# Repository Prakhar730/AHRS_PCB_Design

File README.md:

<div align="center">

# PCB Design for an Attitude and Heading Reference System (AHRS)

### A custom 4-layer PCB featuring an STM32 MCU and a 9-axis IMU, developed during a research internship at the Indian Institute of Technology, Kanpur.

</div>

---

Welcome to the official repository for my AHRS project. This project documents the complete hardware design cycle—from component selection and circuit simulation to final PCB layout—for a custom Attitude and Heading Reference System. It was developed as the primary focus of my six-week internship in the Department of Electrical Engineering at IIT Kanpur.

> The goal of this project was to apply theoretical knowledge of electronics and embedded systems to a practical challenge: creating a compact, reliable, and manufacturable PCB for high-performance orientation sensing in robotics and navigation applications.

---

## Table of Contents
1.  [Key Features](#-key-features)
2.  [Repository Structure](#-repository-structure)
3.  [Technical Specifications](#-technical-specifications)
4.  [Challenges & Solutions](#-challenges--solutions)
5.  [Contact & Acknowledgments](#-contact--acknowledgments)

---

##  Key Features

-   **High-Performance Sensing**: Integrates the `LSM9DS1` 9-axis IMU, which includes a 3-axis accelerometer, 3-axis gyroscope, and 3-axis magnetometer on a single chip.
-   **Powerful Processing**: Driven by an `STM32F401RET6` ARM Cortex-M4 microcontroller, providing ample computational power for real-time sensor fusion algorithms.
-   **Stable Power Management**: Features an onboard `TPS62172` buck converter to efficiently step down 5V from USB to a clean 3.3V supply, validated through LTspice simulations.
-   **Robust Connectivity**: Equipped with a `CP2102` USB-to-UART bridge for straightforward data streaming, programming, and debugging.
-   **Optimized 4-Layer PCB**: The layout is designed for a compact form factor while maintaining excellent signal integrity and noise immunity through dedicated ground and power planes.

---

##  Repository Structure

The project files are organized into two primary directories, separating the hardware design from the circuit simulation.

```
AHRS-PCB-Design/
├── PCB + Schematics/
│   ├── AHRSNEW.kicad_pro
│   ├── AHRSNEW.kicad_sch
│   └── AHRSNEW.kicad_pcb
│
└── Power Supply Simulation/
    └── Draft1.asc
```
-   **`PCB + Schematics/`**: This directory contains the complete KiCad project, including all source files for the schematic design and the final 4-layer PCB layout.
-   **`Power Supply Simulation/`**: This directory holds the LTspice simulation files used to validate the power supply circuit before finalizing the hardware design.

---

##  Technical Specifications

### Hardware Components

| Component         | Part Number       | Description                                                 |
| :---------------- | :---------------- | :---------------------------------------------------------- |
| **Microcontroller** | `STM32F401RET6`     | ARM Cortex-M4 MCU for processing sensor data.               |
| **IMU Sensor** | `LSM9DS1`         | 9-axis motion sensor (accelerometer, gyroscope, magnetometer). |
| **Buck Converter** | `TPS62172`        | Efficiently steps down 5V USB power to a stable 3.3V.       |
| **USB-UART Bridge** | `CP2102`          | Provides a communication interface with a host computer.    |

### Software & Tools

-   **PCB Design**: KiCad (Schematic Capture & PCB Layout)
-   **Circuit Simulation**: LTspice (Power Supply Validation)

---

##  Challenges & Solutions

-   **Interpreting Complex Datasheets**
    -   *Solution*: Adopted a structured approach, breaking down datasheets section-by-section and cross-referencing with application notes and online forums.

-   **Achieving a Stable Power Supply**
    -   *Solution*: The power supply circuit was simulated in LTspice to validate component choices and ensure stable operation before hardware implementation.

-   **PCB Layout & Signal Integrity**
    -   *Solution*: Followed standard PCB best practices, including using differential pair routing for USB, keeping high-speed traces short, and utilizing ground planes to shield signals.

---

##  Contact & Acknowledgments

This project was completed under the expert supervision of Prof. Yatindra Nath Singh at IIT Kanpur. I extend my sincere gratitude to my mentors, Mr. Nagendra Kumar and Mr. Rahul Bhattacharyya, for their continuous technical guidance and support.

Feel free to connect with me to discuss this project or other topics in embedded systems and robotics.

-   **LinkedIn**: [My LinkedIn Profile URL](https://www.linkedin.com/in/prakhar-sharma-75b998347/)
-   **GitHub**: [My GitHub Profile URL](https://github.com/Prakhar730)
-   **Email**: [My Mail](sprakhar2005@gmail.com)

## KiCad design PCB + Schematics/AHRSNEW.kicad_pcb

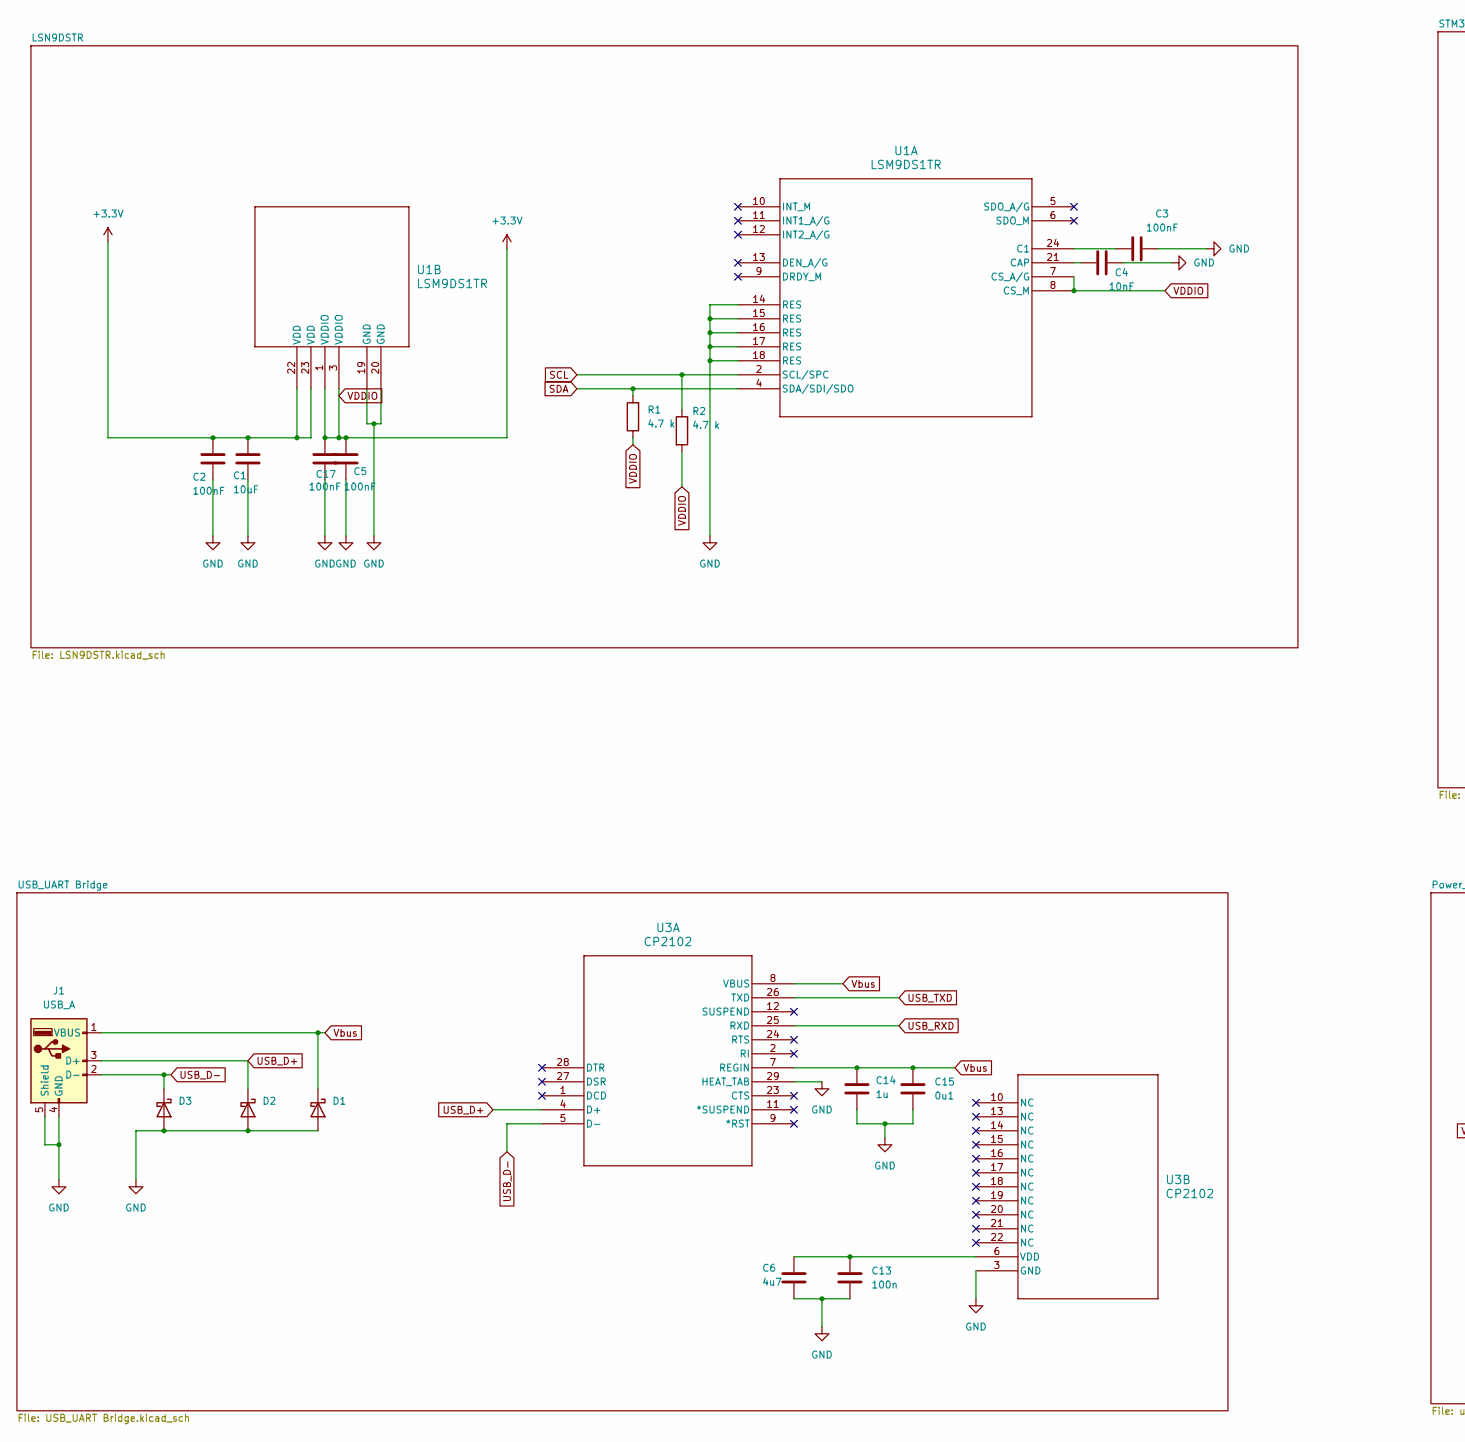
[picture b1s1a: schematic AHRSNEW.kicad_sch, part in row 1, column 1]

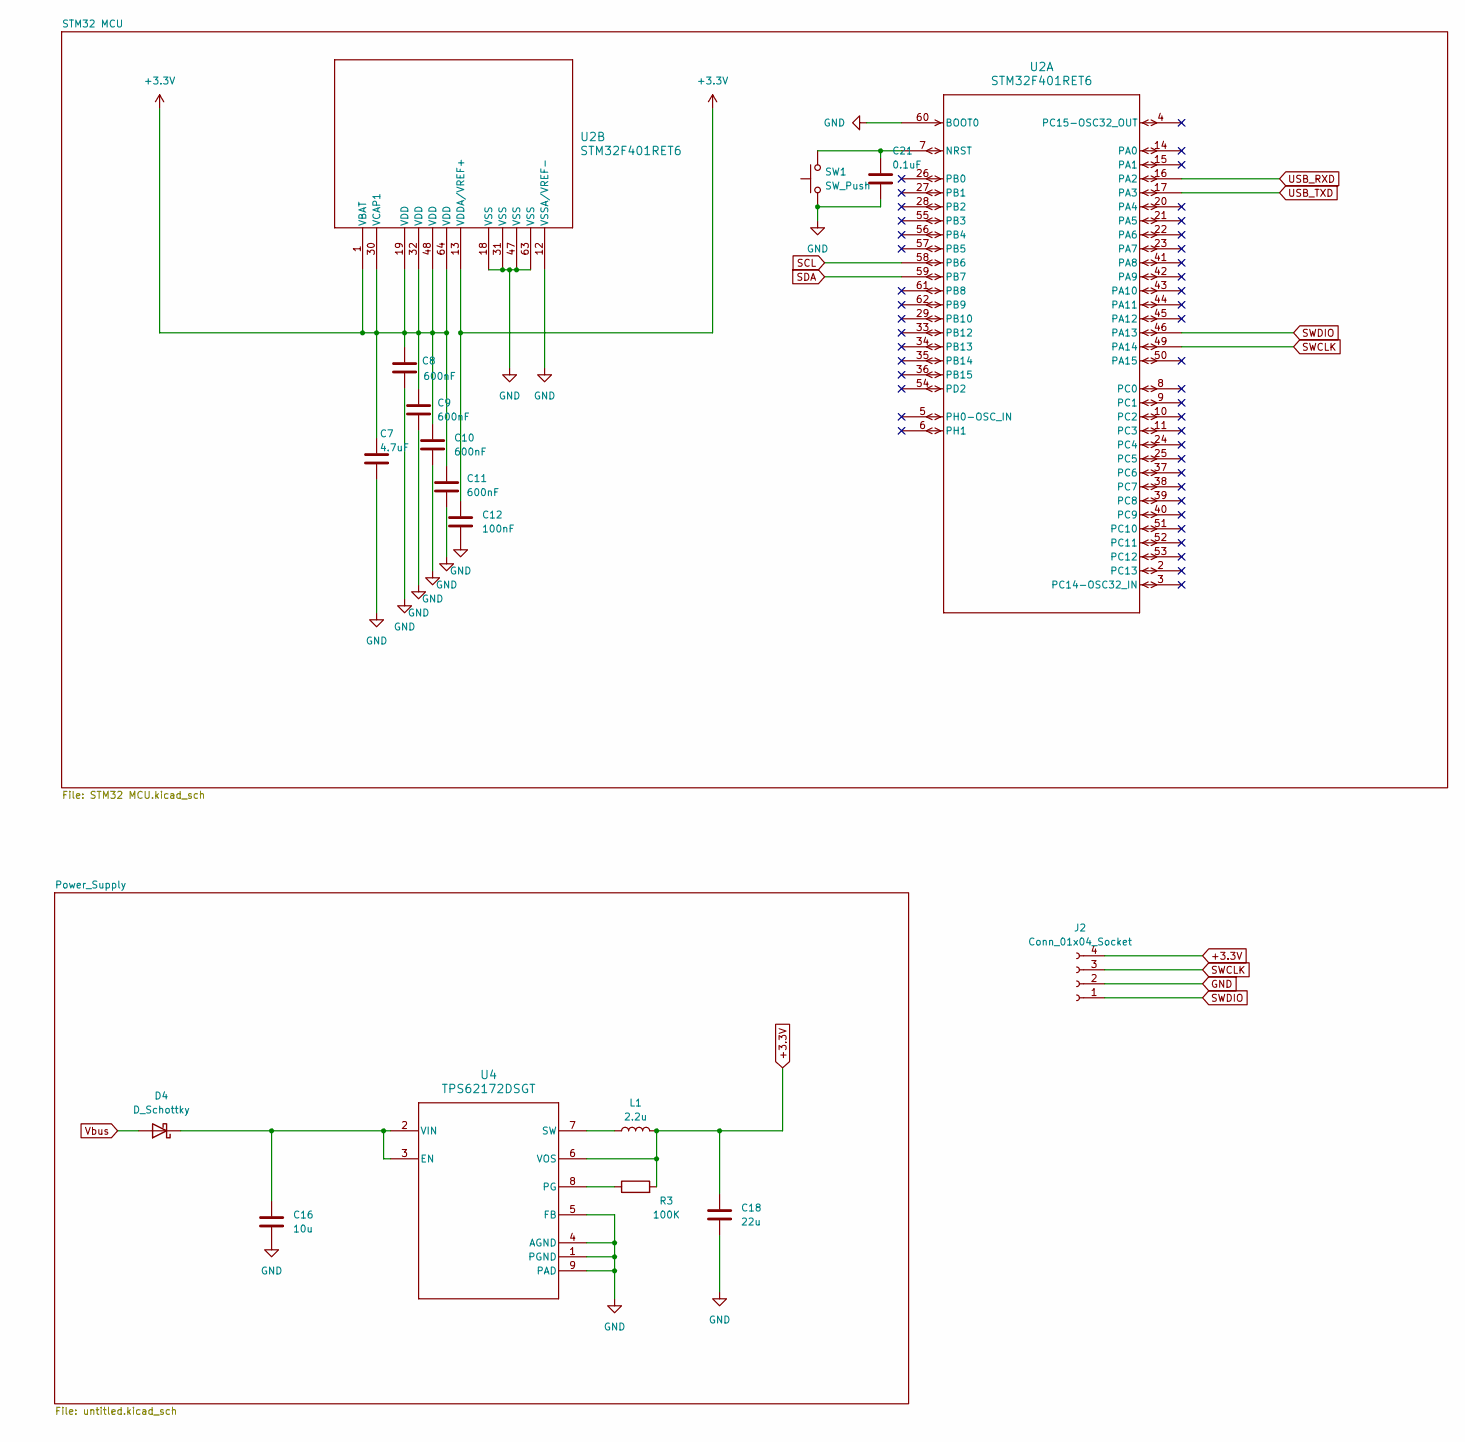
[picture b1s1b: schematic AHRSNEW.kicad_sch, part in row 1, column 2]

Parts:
C1: 10uF; CP_Elec_4x5.3
C2, C3, C5, C12, C17: 100nF; C_0402_1005Metric
C4: 10nF; CP_Elec_3x5.3
C6: 4u7; CP_Elec_4x5.4
C7: 4.7uF; CP_Elec_4x5.4
C8, C9, C10, C11: 600nF; C_1812_4532Metric
C13: 100n; C_0402_1005Metric
C14: 1u; C_0603_1608Metric
C15: 0u1; C_0402_1005Metric
C16: 10u; CP_Elec_4x5.3
C18: 22u; CP_Elec_8x10.5
C21: 0.1uF; C_0402_1005Metric
D1, D2, D3, D4: D_Schottky; D_MicroMELF
J1: USB_A; USB_A_TE_292303-7_Horizontal_fliped
J2: Conn_01x04_Socket; PinHeader_1x04_P2.54mm_Vertical
L1: 2.2u; L_0201_0603Metric
R1, R2: 4.7 k; R_0805_2012Metric
R3: 100K; R_0603_1608Metric
SW1: SW_Push; SW_Push_SPST_NO_Alps_SKRK
U1: LSM9DS1TR; LGA-24_3X3P5X1_STM
U2: STM32F401RET6; LQFP64-10x10mm
U3: CP2102; QFN28N5X5-0p5P_SIL
U4: TPS62172DSGT; DSG0008A

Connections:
+3.3V: C1.1, C2.1, C5.1, C7.1, C8.1, C9.1, C10.1, C11.1, C12.1, C17.1, C18.2, J2.4, L1.2, R1.1, R2.2, R3.2, U1.1 (VDDIO), U1.3 (VDDIO), U1.7 (CS_A/G), U1.8 (CS_M), U1.22 (VDD), U1.23 (VDD), U2.1 (VBAT), U2.13 (VDDA/VREF+), U2.19 (VDD), U2.30 (VCAP1), U2.32 (VDD), U2.48 (VDD), U2.64 (VDD), U4.6 (VOS)
GND: C1.2, C2.2, C3.2, C4.2, C5.2, C6.2, C7.2, C8.2, C9.2, C10.2, C11.2, C12.2, C13.2, C14.2, C15.2, C16.2, C17.2, C18.1, C21.2, D1.2 (A), D2.2 (A), D3.2 (A), J1.4 (GND), J1.5 (Shield), J2.2, SW1.1, U1.14 (RES), U1.15 (RES), U1.16 (RES), U1.17 (RES), U1.18 (RES), U1.19 (GND), U1.20 (GND), U2.12 (VSSA/VREF-), U2.18 (VSS), U2.31 (VSS), U2.47 (VSS), U2.60 (BOOT0), U2.63 (VSS), U3.3 (GND), U3.29 (HEAT_TAB), U4.1 (PGND), U4.4 (AGND), U4.5 (FB), U4.9 (PAD)
unnamed: C16.1, D4.1 (K), U4.2 (VIN), U4.3 (EN)
unnamed: C3.1, U1.24 (C1)
unnamed: C4.1, U1.21 (CAP)
unnamed: C21.1, SW1.2, U2.7 (NRST)
unnamed: C6.1, C13.1, U3.6 (VDD)
unnamed: R3.1, U4.8 (PG)
unnamed: L1.1, U4.7 (SW)
SCL: R2.1, U1.2 (SCL/SPC), U2.58 (PB6)
SDA: R1.2, U1.4 (SDA/SDI/SDO), U2.59 (PB7)
SWCLK: J2.3, U2.49 (PA14)
SWDIO: J2.1, U2.46 (PA13)
USB_D+: D2.1 (K), J1.3 (D+), U3.4 (D+)
USB_D-: D3.1 (K), J1.2 (D-), U3.5 (D-)
USB_RXD: U2.16 (PA2), U3.25 (RXD)
USB_TXD: U2.17 (PA3), U3.26 (TXD)
Vbus: C14.1, C15.1, D1.1 (K), D4.2 (A), J1.1 (VBUS), U3.7 (REGIN), U3.8 (VBUS)

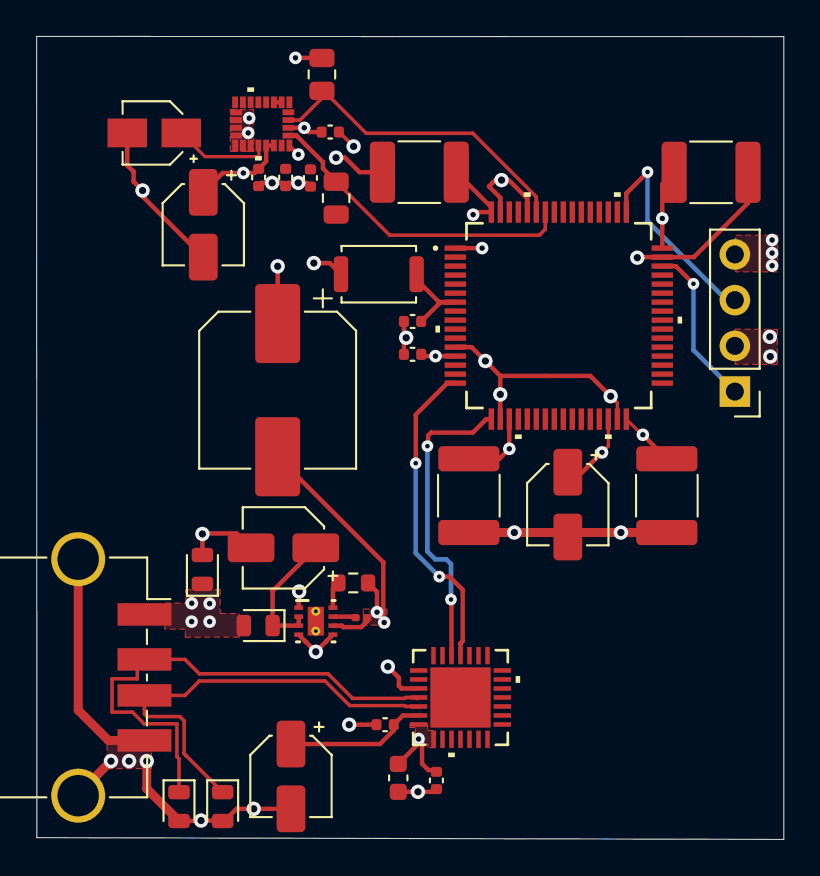
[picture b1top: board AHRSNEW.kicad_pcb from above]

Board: 4 copper layers, 41.5 x 44.6 mm, 34 parts (0 on the bottom side), 18 nets.

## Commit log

2026-03-06 Refactor section headings in README.md
    Updated section headings in README for consistency.
